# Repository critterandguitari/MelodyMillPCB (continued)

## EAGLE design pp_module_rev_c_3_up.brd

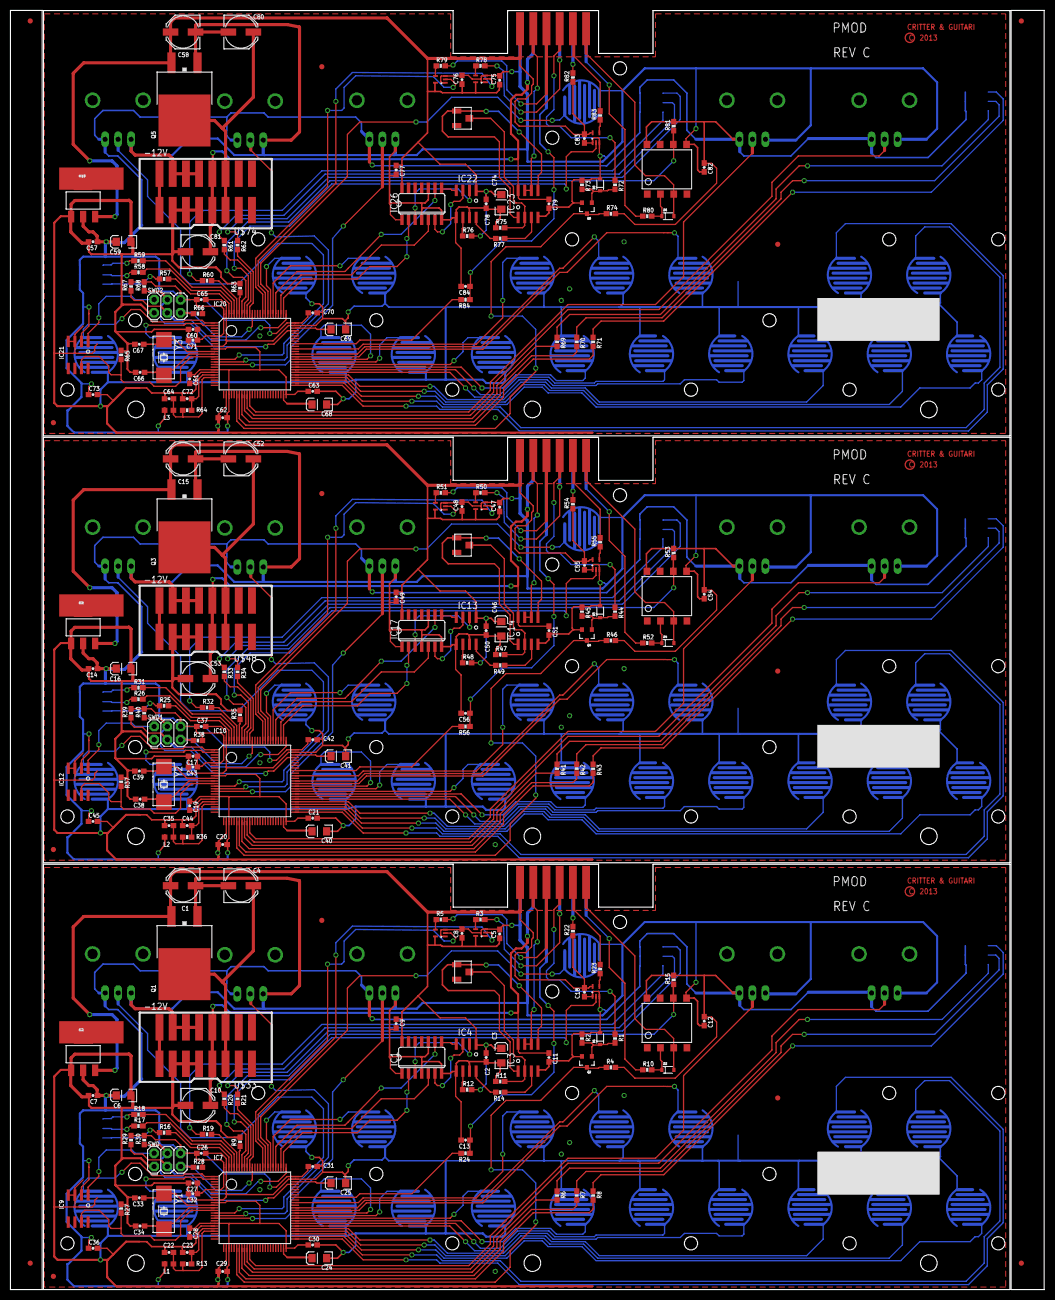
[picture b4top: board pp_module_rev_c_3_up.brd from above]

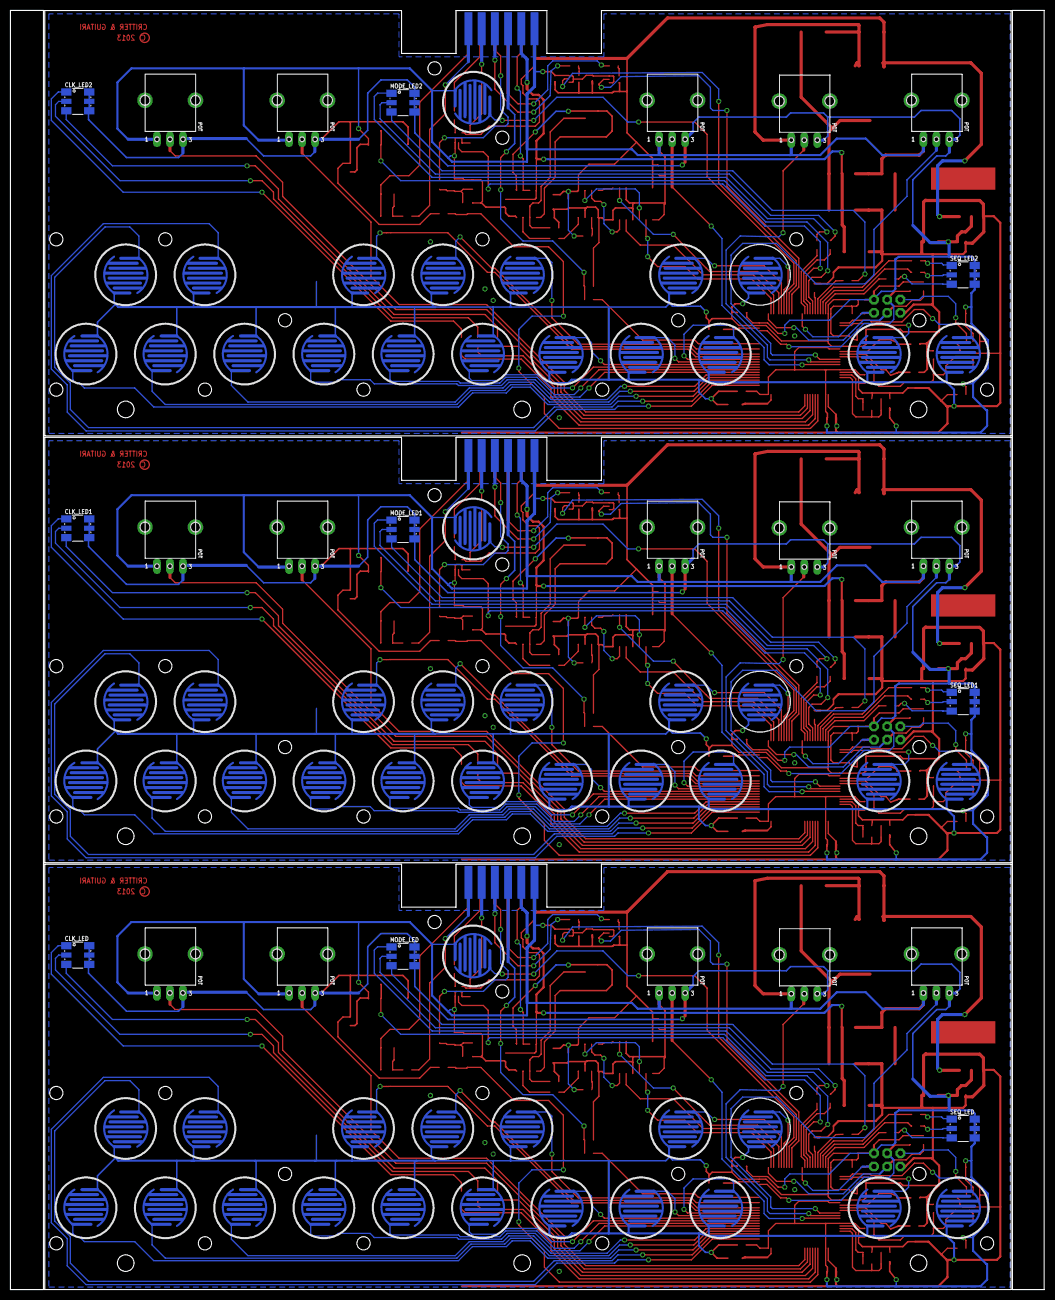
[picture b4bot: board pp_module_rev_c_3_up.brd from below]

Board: 2 copper layers, 198.7 x 245.9 mm, 325 parts (81 on the bottom side), 273 nets.

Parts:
C1, C4, C10, C15, C52, C53, C58, C80, C81: 100u; PANASONIC_D
C2, C5, C7, C8, C9, C11, C12, C13, C14, C17, C18, C19, C20, C21, C22, C23, C26, C27, C28, C29, C30, C31, C32, C35, C36, C37, C42, C43, C44, C45, C47, C48, C49, C50, C51, C54, C55, C56, C57, C60, C61, C62, C63, C64, C65, C70, C71, C72, C73, C75, C76, C77, C78, C79, C82, C83, C84: 100n; 0603-CAP
C3, C6, C16, C24, C25, C40, C41, C46, C59, C68, C69, C74: 10u; EIA3216
C33, C34, C38, C39, C66, C67: 22p; 0603-CAP
CLK_LED, CLK_LED1, CLK_LED2: LED-TRICOLOR-5050
D1, D2, D3, D4, D5, D6: SOD-323
DUR, DUR1, DUR2: POTVERT; POT-P09X-VERT
E$1, E$2, E$3, E$4: FIDUCIAL_1MM
GLIDE, GLIDE1, GLIDE2: POTVERT; POT-P09X-VERT
IC1, IC17, IC26: 74125SO14; SO14
IC2, IC8, IC19: SOT223
IC3, IC14, IC23: SO08
IC4, IC13, IC22: MCP4821; SO08
IC5, IC6, IC11, IC15, IC16, IC18, IC24, IC25, IC27: 741G125SC70; SC-70
IC7, IC10, IC20: STM32F407VGT6; LQFP100-14X14
IC9, IC12, IC21: MAX708; SO08
L1, L2, L3: 10uH; 0603
MODE, MODE1, MODE2: KEY_SWITCH_RUBBER; KEY_CONTACT_RUBBER
MODE_LED, MODE_LED1, MODE_LED2: LED-TRICOLOR-5050
Q1, Q3, Q5: MOSFET-PCHANNELDPAK2; DPAK2
Q2, Q4, Q6: SOT23-3
R1, R2, R3, R4, R5, R6, R7, R8, R9, R16, R17, R18, R19, R20, R21, R25, R26, R31, R32, R33, R34, R35, R41, R42, R43, R44, R45, R46, R50, R51, R57, R58, R59, R60, R61, R62, R63, R69, R70, R71, R72, R73, R74, R78, R79: 1k; 0603-RES
R10, R15, R22, R23, R52, R53, R54, R55, R80, R81, R82, R83: 220; 0603-RES
R11, R13, R36, R47, R64, R75: 4.7k; 0603-RES
R12, R14, R24, R27, R28, R29, R30, R37, R38, R39, R40, R48, R49, R56, R65, R66, R67, R68, R76, R77, R84: 10k; 0603-RES
RANGE, RANGE1, RANGE2: POTVERT; POT-P09X-VERT
RATE, RATE1, RATE2: POTVERT; POT-P09X-VERT
SEQ_LED, SEQ_LED1, SEQ_LED2: LED-TRICOLOR-5050
SWD, SWD1, SWD2: SWD6PIN; 2X3
TUNE, TUNE1, TUNE2: POTVERT; POT-P09X-VERT
U$1, U$23, U$24, U$45, U$47, U$52, U$71, U$73, U$78: FIDUCIAL; FIDUCIAL_1MM
U$2, U$49, U$75: POTSMD-TRIMMER; POT-TRIM-TT-43
U$3, U$50, U$76: CARDEDGE_12POS_MALE
U$4, U$51, U$77: OPTO_DARL_6N138S; 8-SMD
U$5, U$6, U$7, U$8, U$9, U$10, U$11, U$12, U$13, U$14, U$15, U$16, U$17, U$18, U$19, U$20, U$21, U$22, U$26, U$27, U$28, U$29, U$30, U$31, U$32, U$34, U$35, U$36, U$37, U$38, U$39, U$40, U$41, U$42, U$43, U$44, U$53, U$54, U$55, U$56, U$57, U$58, U$59, U$60, U$61, U$62, U$63, U$64, U$65, U$66, U$67, U$68, U$69, U$70: KEY_SWITCH_RUBBER; KEY_CONTACT_RUBBER
U$25, U$46, U$72: LOGOCG; LOGO-CG
U$33, U$48, U$74: DOEPFER_16_CONNSMD; 2X8SMD
Y1, Y2, Y3: CRYSTAL-SMD

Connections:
1V/OCT_J: IC3.6, IC3.7, U$3.9
1V/OCT_J1: IC14.6, IC14.7, U$50.9
1V/OCT_J2: IC23.6, IC23.7, U$76.9
+3.3V: C6.A, C7.1, C12.1, C26.1, C27.1, C28.1, C29.1, C30.1, C31.1, C32.1, C36.1, CLK_LED.1, CLK_LED.3, CLK_LED.5, DUR.3, GLIDE.3, IC2.2, IC7.6, IC7.11, IC7.19, IC7.28, IC7.50, IC7.75, IC7.100, IC9.2, L1.1, MODE_LED.1, MODE_LED.3, MODE_LED.5, R4.2, R15.2, R28.2, R29.2, R30.2, RANGE.3, RATE.3, SEQ_LED.1, SEQ_LED.3, SEQ_LED.5, SWD.6, TUNE.3, U$4.8
+3.3V1: C14.1, C16.A, C17.1, C19.1, C20.1, C21.1, C37.1, C42.1, C43.1, C45.1, C54.1, CLK_LED1.1, CLK_LED1.3, CLK_LED1.5, DUR1.3, GLIDE1.3, IC8.2, IC10.6, IC10.11, IC10.19, IC10.28, IC10.50, IC10.75, IC10.100, IC12.2, L2.1, MODE_LED1.1, MODE_LED1.3, MODE_LED1.5, R38.2, R39.2, R40.2, R46.2, R53.2, RANGE1.3, RATE1.3, SEQ_LED1.1, SEQ_LED1.3, SEQ_LED1.5, SWD1.6, TUNE1.3, U$51.8
+3.3V2: C57.1, C59.A, C60.1, C61.1, C62.1, C63.1, C65.1, C70.1, C71.1, C73.1, C82.1, CLK_LED2.1, CLK_LED2.3, CLK_LED2.5, DUR2.3, GLIDE2.3, IC19.2, IC20.6, IC20.11, IC20.19, IC20.28, IC20.50, IC20.75, IC20.100, IC21.2, L3.1, MODE_LED2.1, MODE_LED2.3, MODE_LED2.5, R66.2, R67.2, R68.2, R74.2, R81.2, RANGE2.3, RATE2.3, SEQ_LED2.1, SEQ_LED2.3, SEQ_LED2.5, SWD2.6, TUNE2.3, U$77.8
+5V: C1.+, C2.1, C3.A, C5.1, C8.1, C9.1, C18.1, IC1.14, IC2.3, IC4.1, IC5.5, IC6.5, IC11.5, Q1.3, R12.2, R22.1, U$3.11
+5V1: C15.+, C46.A, C47.1, C48.1, C49.1, C50.1, C55.1, IC8.3, IC13.1, IC15.5, IC16.5, IC17.14, IC18.5, Q3.3, R48.2, R54.1, U$50.11
+5V2: C58.+, C74.A, C75.1, C76.1, C77.1, C78.1, C83.1, IC19.3, IC22.1, IC24.5, IC25.5, IC26.14, IC27.5, Q5.3, R76.2, R82.1, U$76.11
+12V: C10.+, C11.1, IC3.8, U$3.10, U$33.P$4, U$33.P$12
+12V1: C51.1, C53.+, IC14.8, U$48.P$4, U$48.P$12, U$50.10
+12V2: C79.1, C81.+, IC23.8, U$74.P$4, U$74.P$12, U$76.10
-12V: U$33.P$8, U$33.P$16
-12V1: U$48.P$8, U$48.P$16
-12V2: U$74.P$8, U$74.P$16
CLKIN: IC7.31, Q2.3, R4.1
CLKIN1: IC10.31, Q4.3, R46.1
CLKIN2: IC20.31, Q6.3, R74.1
CLKIN_J: R1.1, U$3.5
CLKIN_J1: R44.1, U$50.5
CLKIN_J2: R72.1, U$76.5
CLK_LED_1: IC7.34, R6.2
CLK_LED_2: IC7.33, R7.2
CLK_LED_3: IC7.32, R8.2
CLK_LED_4: IC10.34, R41.2
CLK_LED_5: IC10.33, R42.2
CLK_LED_6: IC10.32, R43.2
CLK_LED_7: IC20.34, R69.2
CLK_LED_8: IC20.33, R70.2
CLK_LED_9: IC20.32, R71.2
DAC_CS: IC1.2, IC7.77
DAC_CS1: IC10.77, IC17.2
DAC_CS2: IC20.77, IC26.2
DAC_MOSI: IC1.9, IC7.80
DAC_MOSI1: IC10.80, IC17.9
DAC_MOSI2: IC20.80, IC26.9
DAC_OUT: IC4.8, R14.2
DAC_OUT1: IC13.8, R49.2
DAC_OUT2: IC22.8, R77.2
DAC_SCK: IC1.5, IC7.78
DAC_SCK1: IC10.78, IC17.5
DAC_SCK2: IC20.78, IC26.5
DUR: DUR.WIPER, IC7.15
DUR1: DUR1.WIPER, IC10.15
DUR2: DUR2.WIPER, IC20.15
GATE: IC5.2, IC7.85
GATE1: IC10.85, IC16.2
GATE2: IC20.85, IC25.2
GATE_J: R5.2, U$3.7
GATE_J1: R51.2, U$50.7
GATE_J2: R79.2, U$76.7
GLIDE: GLIDE.WIPER, IC7.16
GLIDE1: GLIDE1.WIPER, IC10.16
GLIDE2: GLIDE2.WIPER, IC20.16
GND: C1.-, C2.2, C3.C, C4.-, C5.2, C6.C, C7.2, C8.2, C9.2, C10.-, C11.2, C12.2, C13.2, C18.2, C22.2, C23.2, C24.C, C25.C, C26.2, C27.2, C28.2, C29.2, C30.2, C31.2, C32.2, C33.2, C34.2, C36.2, D1.2, DUR.1, GLIDE.1, IC1.1, IC1.4, IC1.7, IC1.10, IC2.1, IC3.4, IC4.5, IC4.7, IC5.1, IC5.3, IC6.1, IC6.3, IC7.10, IC7.20, IC7.27, IC7.74, IC7.99, IC9.3, IC9.4, IC11.1, IC11.3, MODE.1, Q1.1, Q2.2, R2.1, R9.2, R11.1, R27.1, RANGE.1, RATE.1, SWD.1, TUNE.1, U$3.12, U$4.5, U$5.1, U$6.1, U$7.1, U$8.1, U$9.1, U$10.1, U$11.1, U$12.1, U$13.1, U$14.1, U$15.1, U$16.1, U$17.1, U$18.1, U$19.1, U$20.1, U$21.1, U$22.1, U$33.P$5, U$33.P$6, U$33.P$7, U$33.P$13, U$33.P$14, U$33.P$15
GND1: C14.2, C15.-, C16.C, C17.2, C19.2, C20.2, C21.2, C35.2, C37.2, C38.2, C39.2, C40.C, C41.C, C42.2, C43.2, C44.2, C45.2, C46.C, C47.2, C48.2, C49.2, C50.2, C51.2, C52.-, C53.-, C54.2, C55.2, C56.2, D3.2, DUR1.1, GLIDE1.1, IC8.1, IC10.10, IC10.20, IC10.27, IC10.74, IC10.99, IC12.3, IC12.4, IC13.5, IC13.7, IC14.4, IC15.1, IC15.3, IC16.1, IC16.3, IC17.1, IC17.4, IC17.7, IC17.10, IC18.1, IC18.3, MODE1.1, Q3.1, Q4.2, R35.2, R37.1, R45.1, R47.1, RANGE1.1, RATE1.1, SWD1.1, TUNE1.1, U$26.1, U$27.1, U$28.1, U$29.1, U$30.1, U$31.1, U$32.1, U$34.1, U$35.1, U$36.1, U$37.1, U$38.1, U$39.1, U$40.1, U$41.1, U$42.1, U$43.1, U$44.1, U$48.P$5, U$48.P$6, U$48.P$7, U$48.P$13, U$48.P$14, U$48.P$15, U$50.12, U$51.5
GND2: C57.2, C58.-, C59.C, C60.2, C61.2, C62.2, C63.2, C64.2, C65.2, C66.2, C67.2, C68.C, C69.C, C70.2, C71.2, C72.2, C73.2, C74.C, C75.2, C76.2, C77.2, C78.2, C79.2, C80.-, C81.-, C82.2, C83.2, C84.2, D5.2, DUR2.1, GLIDE2.1, IC19.1, IC20.10, IC20.20, IC20.27, IC20.74, IC20.99, IC21.3, IC21.4, IC22.5, IC22.7, IC23.4, IC24.1, IC24.3, IC25.1, IC25.3, IC26.1, IC26.4, IC26.7, IC26.10, IC27.1, IC27.3, MODE2.1, Q5.1, Q6.2, R63.2, R65.1, R73.1, R75.1, RANGE2.1, RATE2.1, SWD2.1, TUNE2.1, U$53.1, U$54.1, U$55.1, U$56.1, U$57.1, U$58.1, U$59.1, U$60.1, U$61.1, U$62.1, U$63.1, U$64.1, U$65.1, U$66.1, U$67.1, U$68.1, U$69.1, U$70.1, U$74.P$5, U$74.P$6, U$74.P$7, U$74.P$13, U$74.P$14, U$74.P$15, U$76.12, U$77.5
K1: IC7.51, U$5.2
K2: IC7.52, U$7.2
K3: IC7.53, U$9.2
K4: IC7.54, U$11.2
K5: IC7.55, U$13.2
K6: IC7.63, U$15.2
K7: IC7.65, U$17.2
K8: IC7.56, U$19.2
K9: IC7.57, U$6.2
K10: IC7.58, U$8.2
K11: IC7.59, U$10.2
K12: IC7.60, U$12.2
K13: IC7.61, U$14.2
K14: IC7.62, U$16.2
K15: IC7.1, U$18.2
K16: IC7.2, U$20.2
K17: IC7.81, U$21.2
K18: IC7.82, U$22.2
K19: IC10.51, U$26.2
K20: IC10.52, U$27.2
K21: IC10.53, U$28.2
K22: IC10.54, U$29.2
K23: IC10.55, U$30.2
K24: IC10.63, U$31.2
K25: IC10.65, U$32.2
K26: IC10.56, U$34.2
K27: IC10.2, U$42.2
K28: IC10.1, U$41.2
K29: IC10.62, U$40.2
K30: IC10.61, U$39.2
K31: IC10.60, U$38.2
K32: IC10.59, U$37.2
K33: IC10.58, U$36.2
K34: IC10.57, U$35.2
K35: IC10.81, U$43.2
K36: IC10.82, U$44.2
K37: IC20.51, U$53.2
K38: IC20.52, U$54.2
K39: IC20.53, U$55.2
K40: IC20.54, U$56.2
K41: IC20.55, U$57.2
K42: IC20.63, U$58.2
K43: IC20.65, U$59.2
K44: IC20.56, U$60.2
K45: IC20.2, U$68.2
K46: IC20.1, U$67.2
K47: IC20.62, U$66.2
K48: IC20.61, U$65.2
K49: IC20.60, U$64.2
K50: IC20.59, U$63.2
K51: IC20.58, U$62.2
K52: IC20.57, U$61.2
K53: IC20.81, U$69.2
K54: IC20.82, U$70.2
MIDIIN_1: D4.2, U$50.1, U$51.3
MIDIIN_2: R52.1, U$50.2
MIDIIN_3: D6.2, U$76.1, U$77.3
MIDIIN_4: R10.1, U$3.2
MIDIIN_5: D2.2, U$3.1, U$4.3
MIDIIN_6: R80.1, U$76.2
MIDIOUT_1: R55.2, U$50.3
MIDIOUT_2: R54.2, U$50.4
MIDIOUT_3: R83.2, U$76.3
MIDIOUT_4: R22.2, U$3.4
MIDIOUT_5: R23.2, U$3.3
MIDIOUT_6: R82.2, U$76.4
MIDI_RXD: IC7.93, R15.1, U$4.6
MIDI_RXD1: IC10.93, R53.1, U$51.6
MIDI_RXD2: IC20.93, R81.1, U$77.6
MIDI_TXD: IC6.2, IC7.92
MIDI_TXD1: IC10.92, IC18.2
MIDI_TXD2: IC20.92, IC27.2
MODE: IC7.83, MODE.2
MODE1: IC10.83, MODE1.2
MODE2: IC20.83, MODE2.2
MODE_LED_1: IC7.95, R19.2
MODE_LED_2: IC7.91, R20.2
MODE_LED_3: IC7.90, R21.2
MODE_LED_4: IC10.95, R32.2
MODE_LED_5: IC10.91, R33.2
MODE_LED_6: IC10.90, R34.2
MODE_LED_7: IC20.95, R60.2
MODE_LED_8: IC20.91, R61.2
MODE_LED_9: IC20.90, R62.2
MRST: IC9.1, SWD.2
MRST1: IC12.1, SWD1.2
MRST2: IC21.1, SWD2.2
unnamed: MODE_LED.6, R19.1
unnamed: MODE_LED.4, R20.1
unnamed: C34.1, IC7.13, Y1.2
unnamed: MODE_LED.2, R21.1
unnamed: C24.A, IC7.49
unnamed: C33.1, IC7.12, Y1.1
unnamed: IC3.2, R11.2, U$2.2
unnamed: IC3.3, R14.1
unnamed: C4.+, Q1.4, U$33.P$3, U$33.P$11
unnamed: IC11.4, R3.1
unnamed: CLK_LED.6, R6.1
unnamed: IC5.4, R5.1
unnamed: IC7.67, R24.2
unnamed: CLK_LED.4, R7.1
unnamed: CLK_LED.2, R8.1
unnamed: R31.1, SEQ_LED1.2
unnamed: C25.A, IC7.73
unnamed: IC4.6, R12.1
unnamed: R18.1, SEQ_LED.2
unnamed: R17.1, SEQ_LED.4
unnamed: IC7.94, R9.1
unnamed: R16.1, SEQ_LED.6
unnamed: R26.1, SEQ_LED1.4
unnamed: IC3.1, IC3.5, U$2.1
unnamed: R25.1, SEQ_LED1.6
unnamed: MODE_LED1.6, R32.1
unnamed: IC1.3, IC4.2
unnamed: C22.1, IC7.22, L1.2, R13.2
unnamed: C23.1, IC7.21, R13.1
unnamed: D2.1, R10.2, U$4.2
unnamed: MODE_LED1.4, R33.1
unnamed: MODE_LED1.2, R34.1
unnamed: C38.1, IC10.13, Y2.2
unnamed: IC6.4, R23.1
unnamed: C39.1, IC10.12, Y2.1
unnamed: IC1.6, IC4.3
unnamed: IC1.8, IC4.4
unnamed: D1.1, Q2.1, R1.2, R2.2
unnamed: IC10.94, R35.1
unnamed: C41.A, IC10.73
unnamed: C40.A, IC10.49
unnamed: C35.1, IC10.22, L2.2, R36.2
unnamed: C44.1, IC10.21, R36.1
unnamed: IC13.6, R48.1
unnamed: IC14.2, R47.2, U$49.2
unnamed: IC14.3, R49.1
unnamed: C52.+, Q3.4, U$48.P$3, U$48.P$11
unnamed: IC15.4, R50.1
unnamed: IC16.4, R51.1
unnamed: CLK_LED1.6, R41.1
unnamed: CLK_LED1.4, R42.1
unnamed: CLK_LED1.2, R43.1
unnamed: IC14.1, IC14.5, U$49.1
unnamed: IC13.2, IC17.3
unnamed: IC13.3, IC17.6
unnamed: IC13.4, IC17.8
unnamed: D3.1, Q4.1, R44.2, R45.2
unnamed: D4.1, R52.2, U$51.2
unnamed: IC18.4, R55.1
unnamed: IC10.67, R56.2
unnamed: R59.1, SEQ_LED2.2
unnamed: R58.1, SEQ_LED2.4
unnamed: R57.1, SEQ_LED2.6
unnamed: MODE_LED2.6, R60.1
unnamed: MODE_LED2.4, R61.1
unnamed: MODE_LED2.2, R62.1
unnamed: C66.1, IC20.13, Y3.2
unnamed: C67.1, IC20.12, Y3.1
unnamed: IC20.94, R63.1
unnamed: C69.A, IC20.73
unnamed: C68.A, IC20.49
unnamed: C64.1, IC20.22, L3.2, R64.2
unnamed: C72.1, IC20.21, R64.1
unnamed: IC22.6, R76.1
unnamed: IC23.2, R75.2, U$75.2
unnamed: IC23.3, R77.1
unnamed: C80.+, Q5.4, U$74.P$3, U$74.P$11
unnamed: IC24.4, R78.1
unnamed: IC25.4, R79.1
unnamed: CLK_LED2.6, R69.1
unnamed: CLK_LED2.4, R70.1
unnamed: CLK_LED2.2, R71.1
unnamed: IC23.1, IC23.5, U$75.1
unnamed: IC22.2, IC26.3
unnamed: IC22.3, IC26.6
unnamed: IC22.4, IC26.8
unnamed: D5.1, Q6.1, R72.2, R73.2
unnamed: D6.1, R80.2, U$77.2
unnamed: IC27.4, R83.1
unnamed: IC20.67, R84.2
NRST: IC7.14, IC9.7, R27.2
NRST1: IC10.14, IC12.7, R37.2
NRST2: IC20.14, IC21.7, R65.2
PWM_J: C13.1, R24.1, U$3.8
PWM_J1: C56.1, R56.1, U$50.8
PWM_J2: C84.1, R84.1, U$76.8
RANGE: IC7.36, RANGE.WIPER
RANGE1: IC10.36, RANGE1.WIPER
RANGE2: IC20.36, RANGE2.WIPER
RATE: IC7.35, RATE.WIPER
RATE1: IC10.35, RATE1.WIPER
RATE2: IC20.35, RATE2.WIPER
SEQ_LED_1: IC7.98, R16.2
SEQ_LED_2: IC7.97, R17.2
SEQ_LED_3: IC7.96, R18.2
SEQ_LED_4: IC10.98, R25.2
SEQ_LED_5: IC10.97, R26.2
SEQ_LED_6: IC10.96, R31.2
SEQ_LED_7: IC20.98, R57.2
SEQ_LED_8: IC20.97, R58.2
SEQ_LED_9: IC20.96, R59.2
SWDCLK: IC7.76, R29.1, SWD.3
SWDCLK1: IC10.76, R39.1, SWD1.3
SWDCLK2: IC20.76, R67.1, SWD2.3
SWDIO: IC7.72, R30.1, SWD.4
SWDIO1: IC10.72, R40.1, SWD1.4
SWDIO2: IC20.72, R68.1, SWD2.4
SWO: IC7.89, R28.1, SWD.5
SWO1: IC10.89, R38.1, SWD1.5
SWO2: IC20.89, R66.1, SWD2.5
TRIG: IC7.84, IC11.2
TRIG1: IC10.84, IC15.2
TRIG2: IC20.84, IC24.2
TRIG_J: R3.2, U$3.6
TRIG_J1: R50.2, U$50.6
TRIG_J2: R78.2, U$76.6
TUNE: IC7.17, TUNE.WIPER
TUNE1: IC10.17, TUNE1.WIPER
TUNE2: IC20.17, TUNE2.WIPER

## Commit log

2016-05-31 added connector board, BOM
2016-06-01 add license to read me
2016-06-01 added license file
